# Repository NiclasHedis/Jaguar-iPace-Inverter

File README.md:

# Jaguar-iPace-Inverter
Design of Opensource Logic boards to run the Jaguar iPace Inverter and Motors.

PCB Designs in Kicad 9 format.

Front inverter used in the iPace is acuallly a Vitesco EPF2.8+ :
https://vitesco-technologies.com/en/Home/Solutions/Products/High-Voltage-Inverter-(EPF2-8-)-en

Reverse engineering thread on the openinverter forum :
https://openinverter.org/forum/viewtopic.php?f=23&t=1210

Videos :
https://youtu.be/Kg5qWuOF9P8

10/10/25 : Add prelim front drive unit V1 board design (work in progress).

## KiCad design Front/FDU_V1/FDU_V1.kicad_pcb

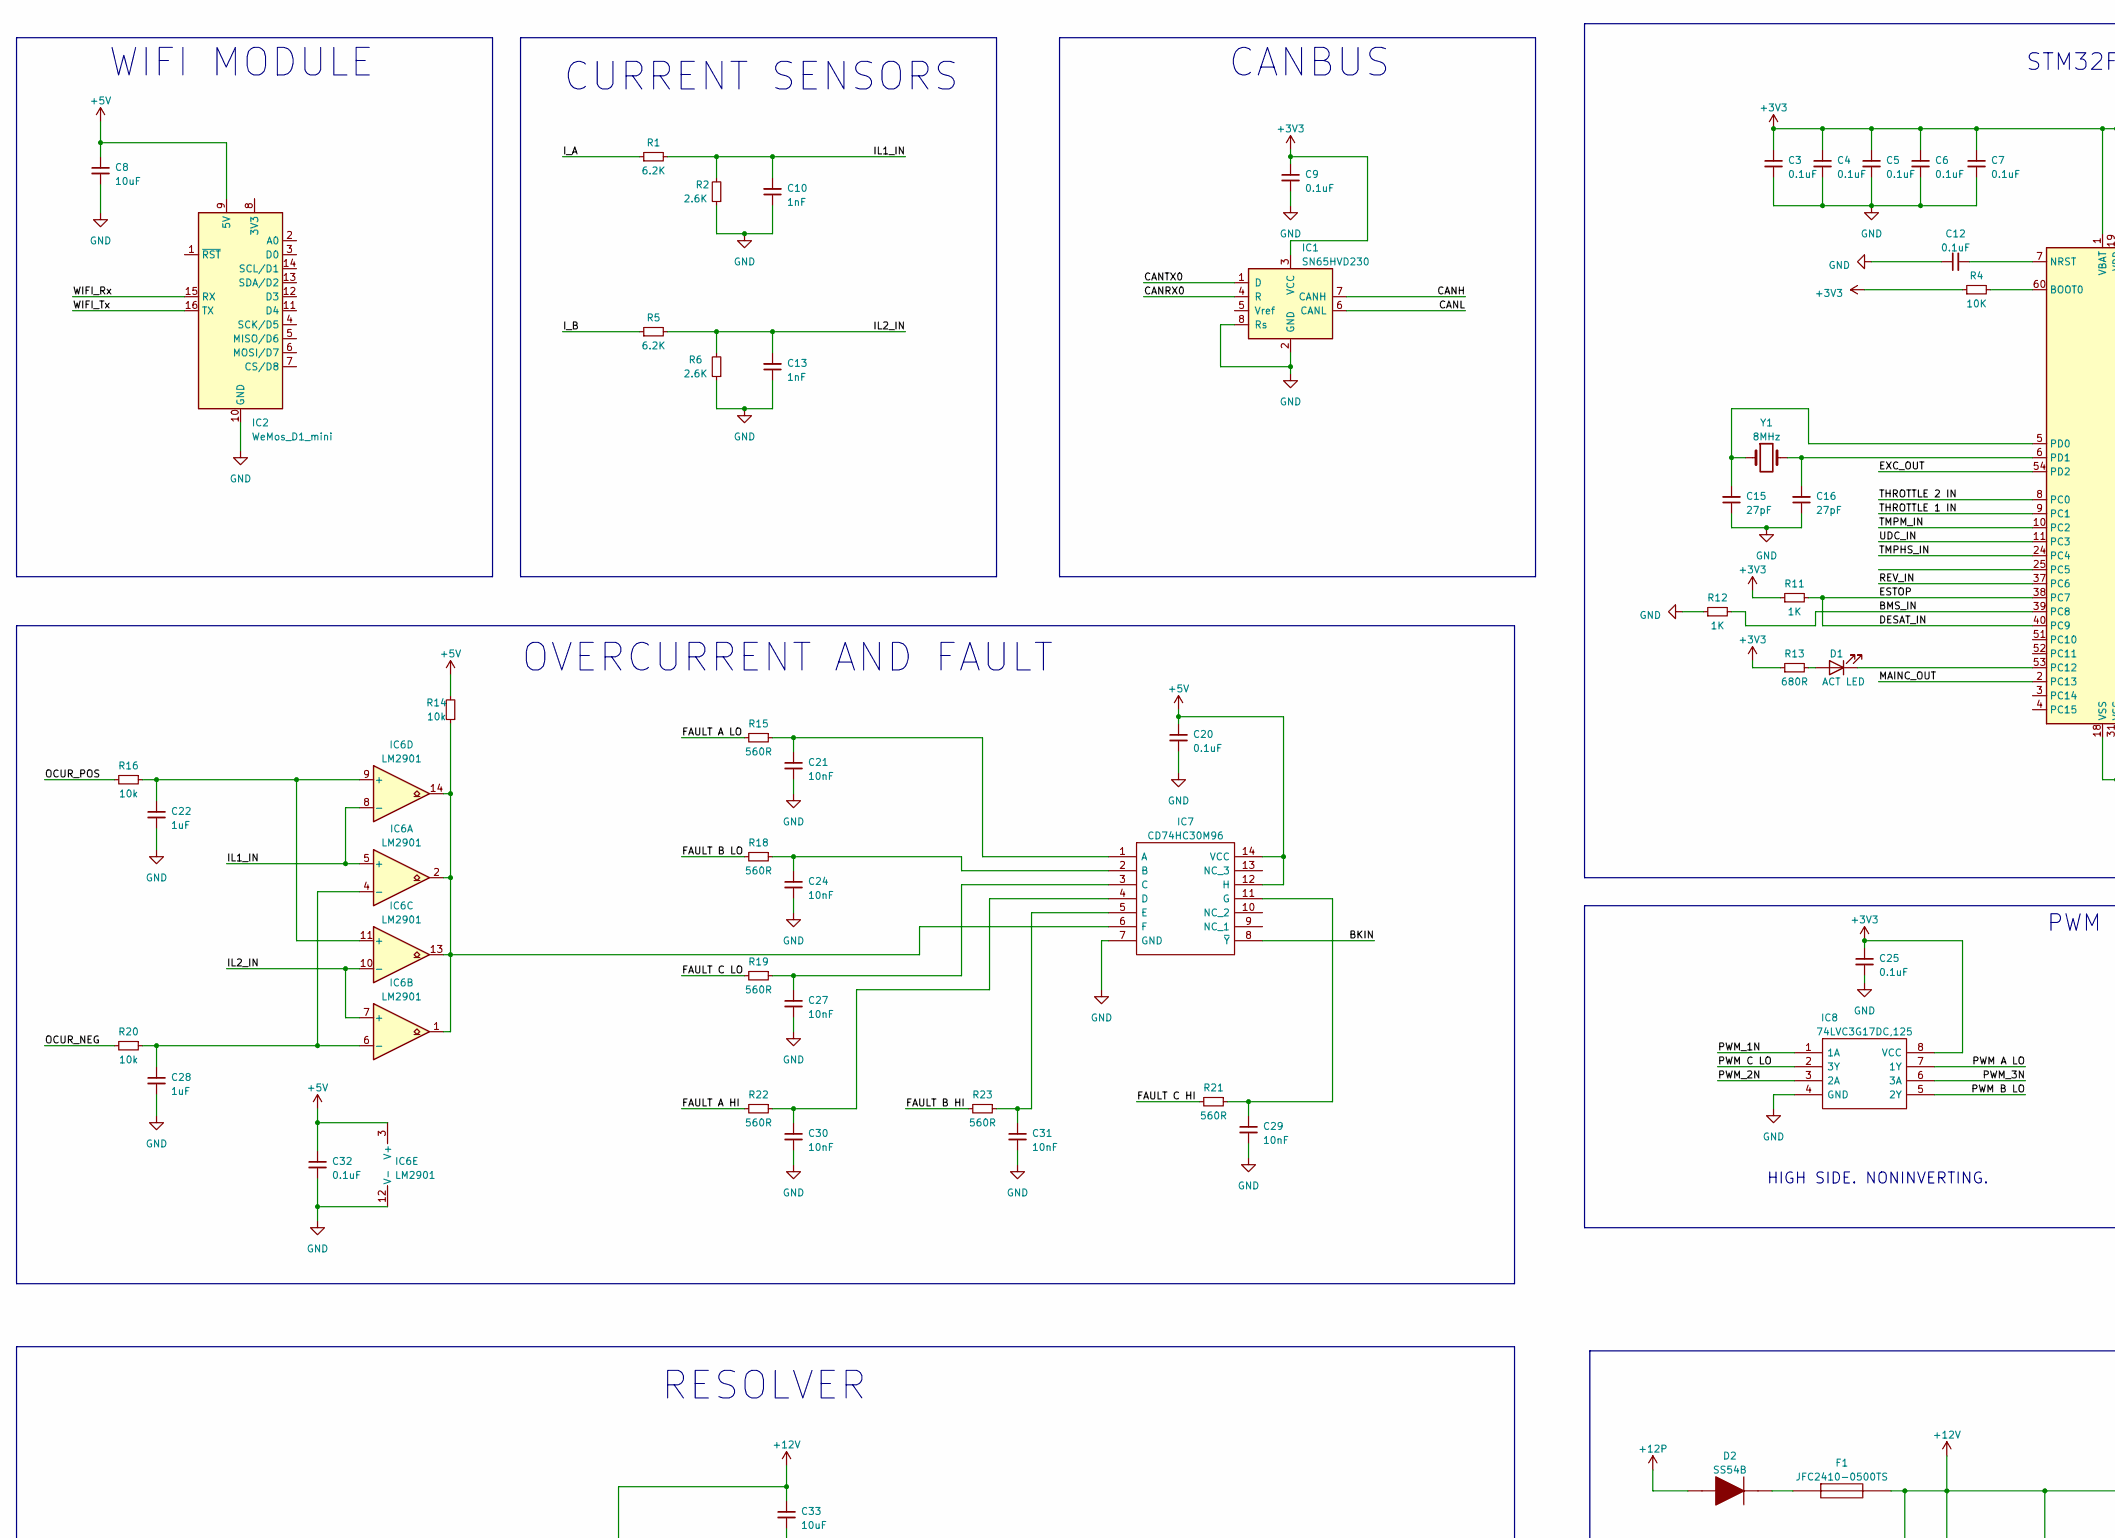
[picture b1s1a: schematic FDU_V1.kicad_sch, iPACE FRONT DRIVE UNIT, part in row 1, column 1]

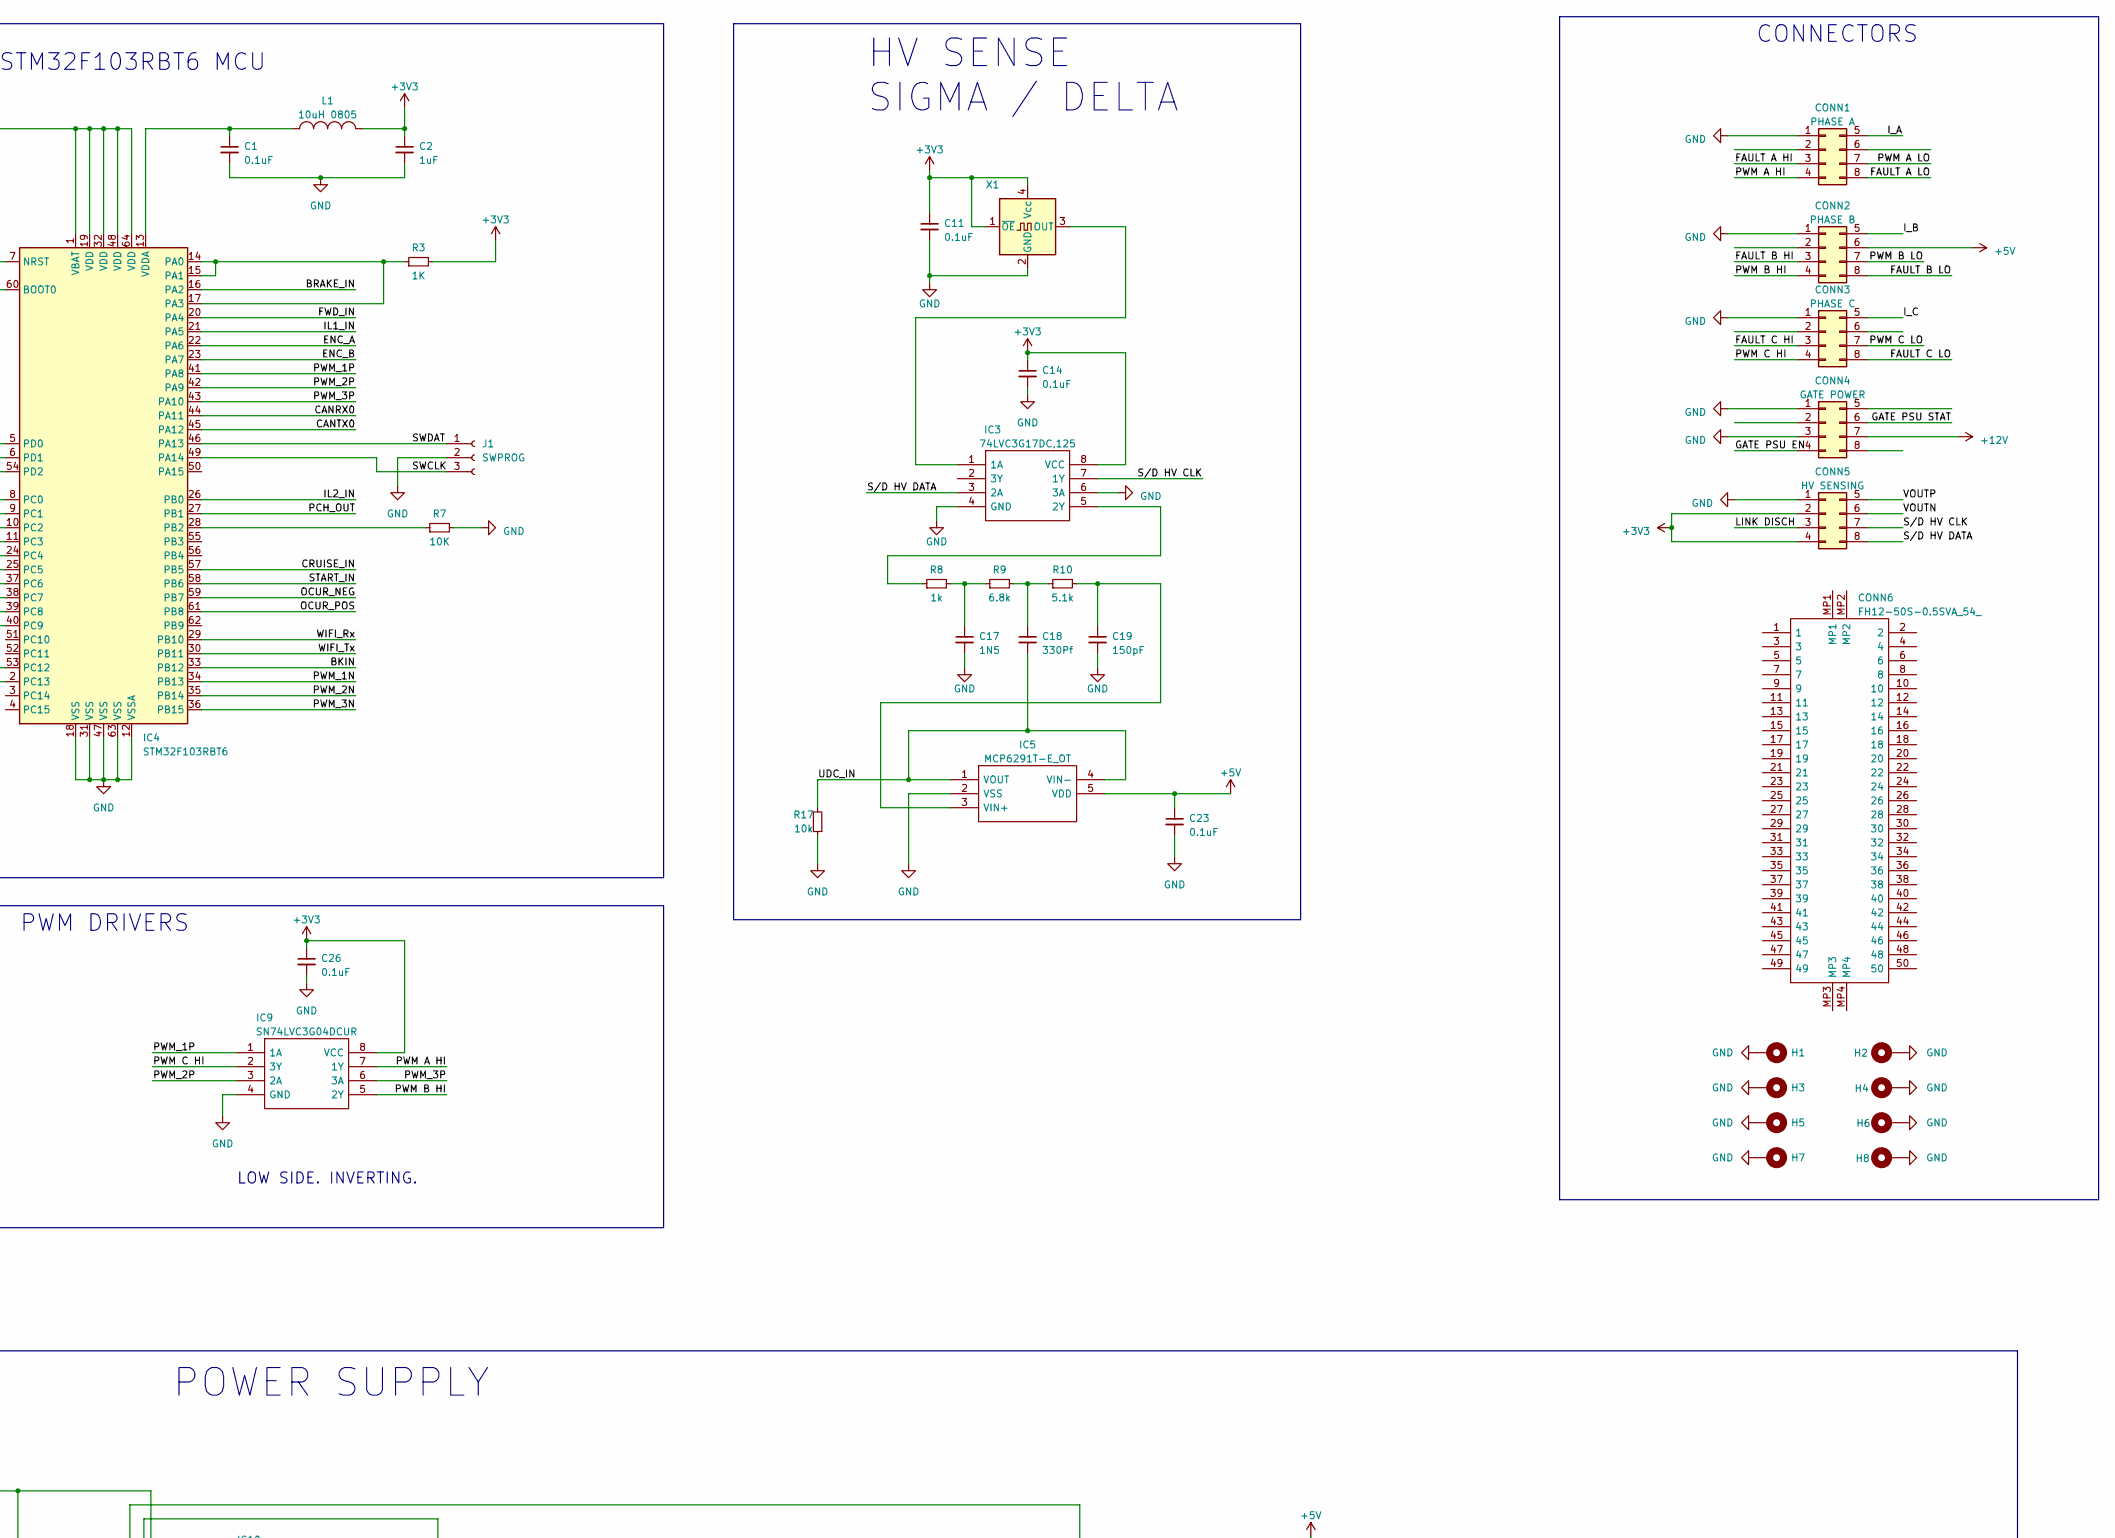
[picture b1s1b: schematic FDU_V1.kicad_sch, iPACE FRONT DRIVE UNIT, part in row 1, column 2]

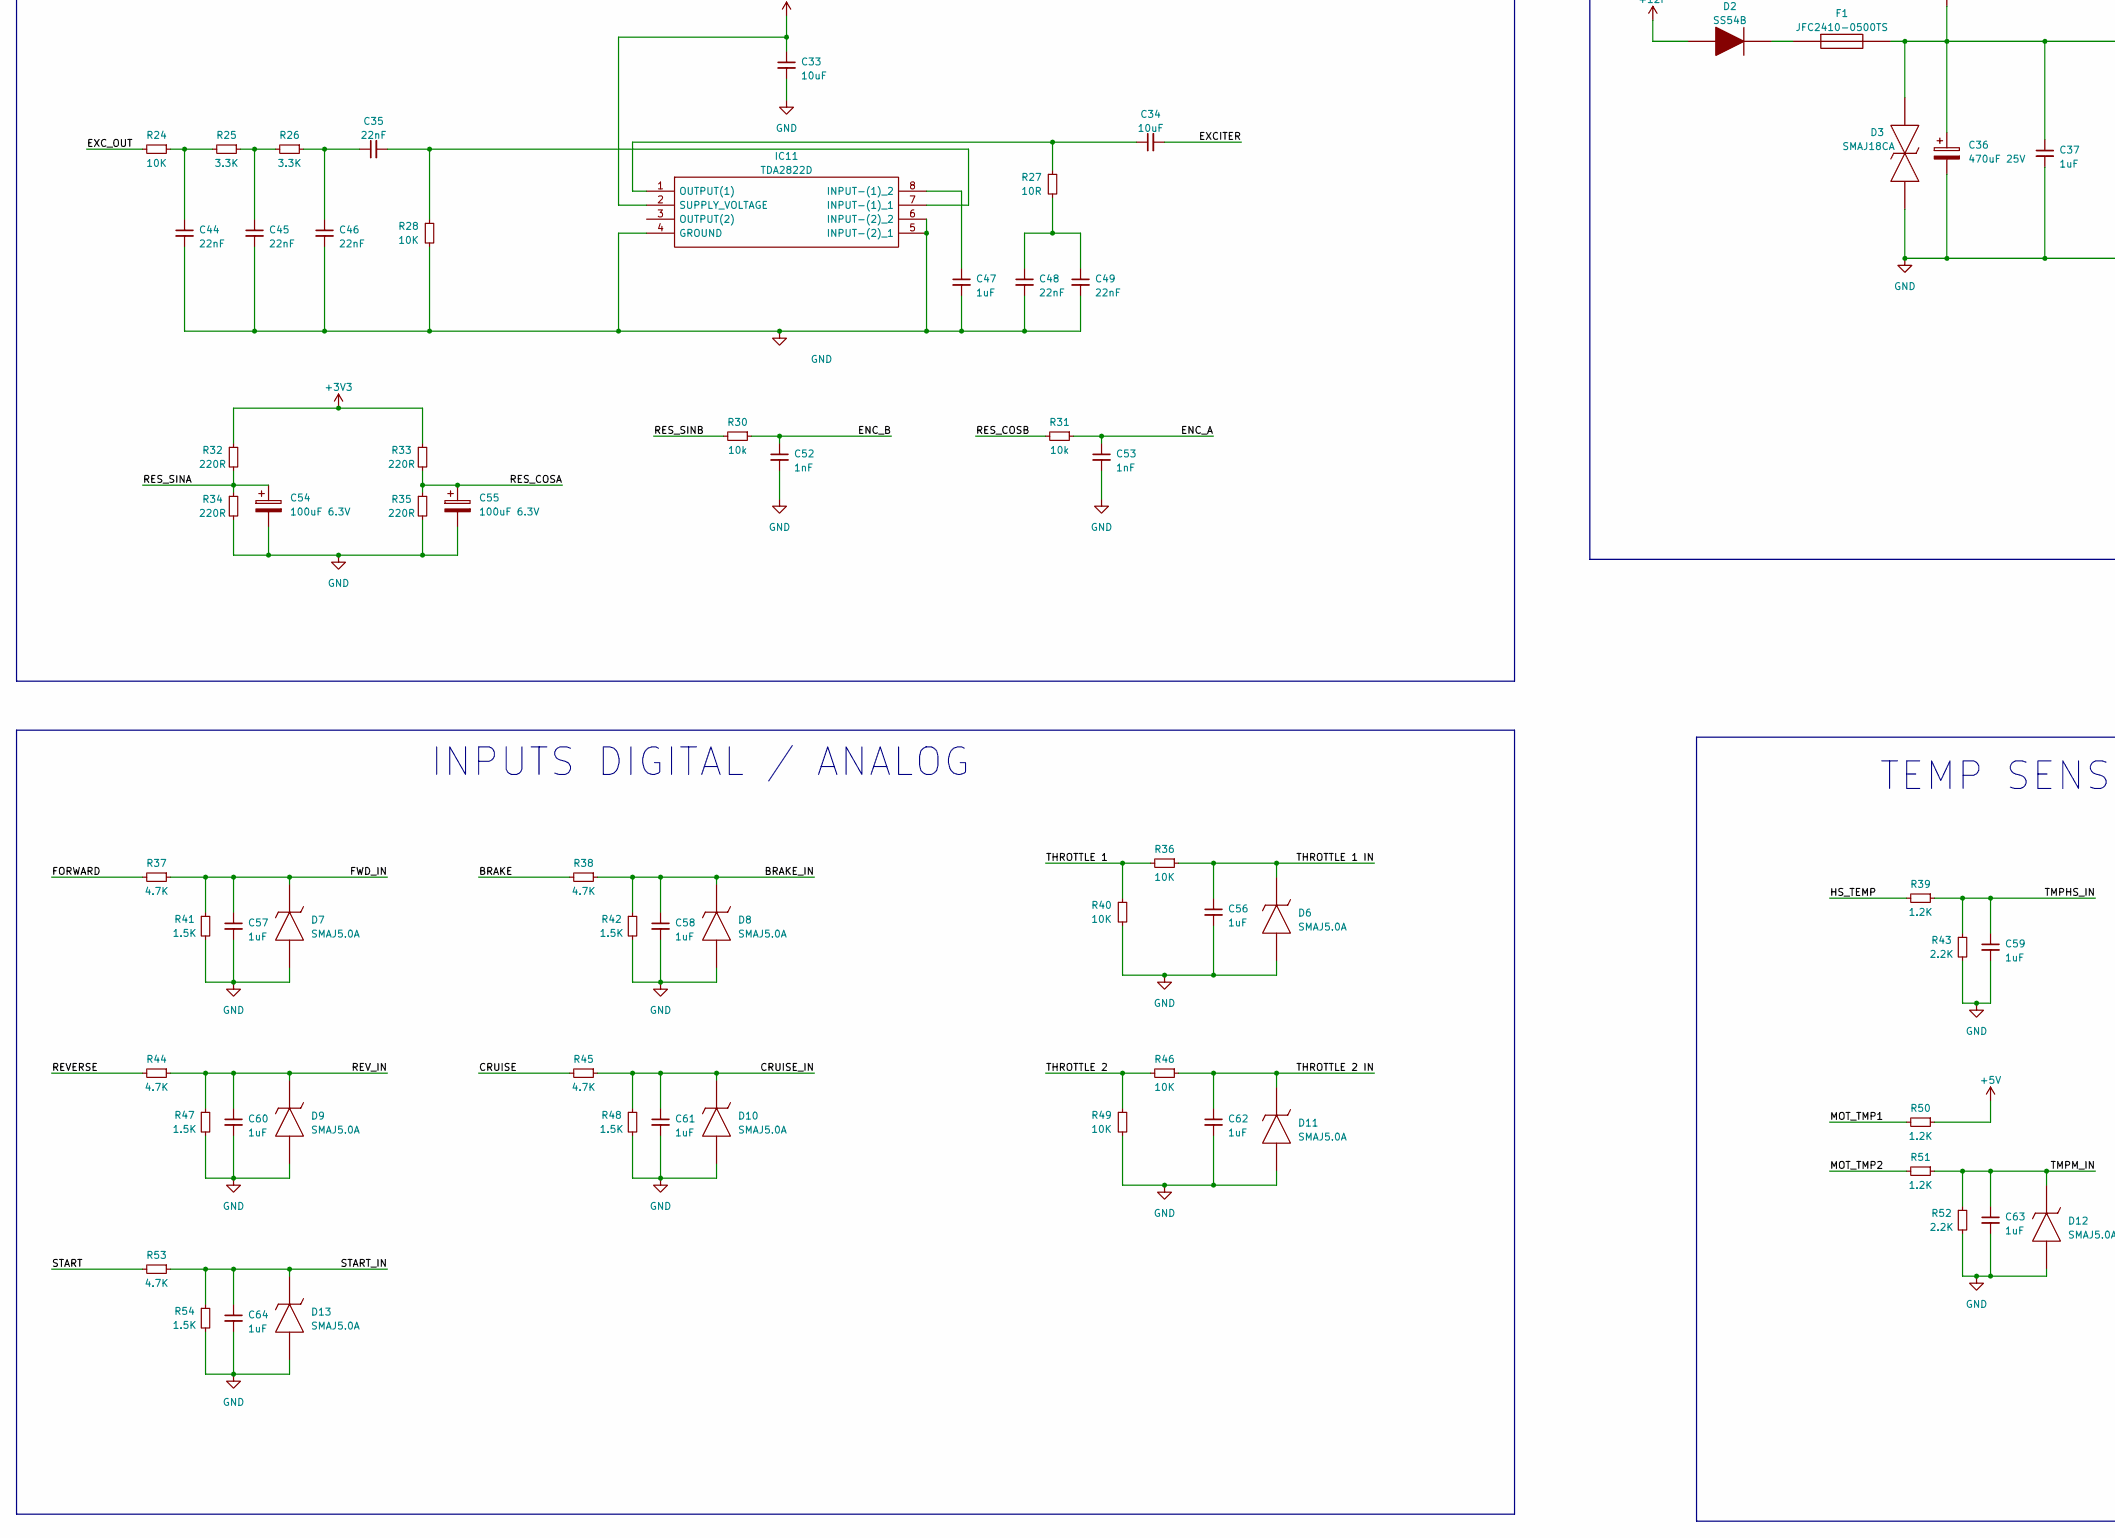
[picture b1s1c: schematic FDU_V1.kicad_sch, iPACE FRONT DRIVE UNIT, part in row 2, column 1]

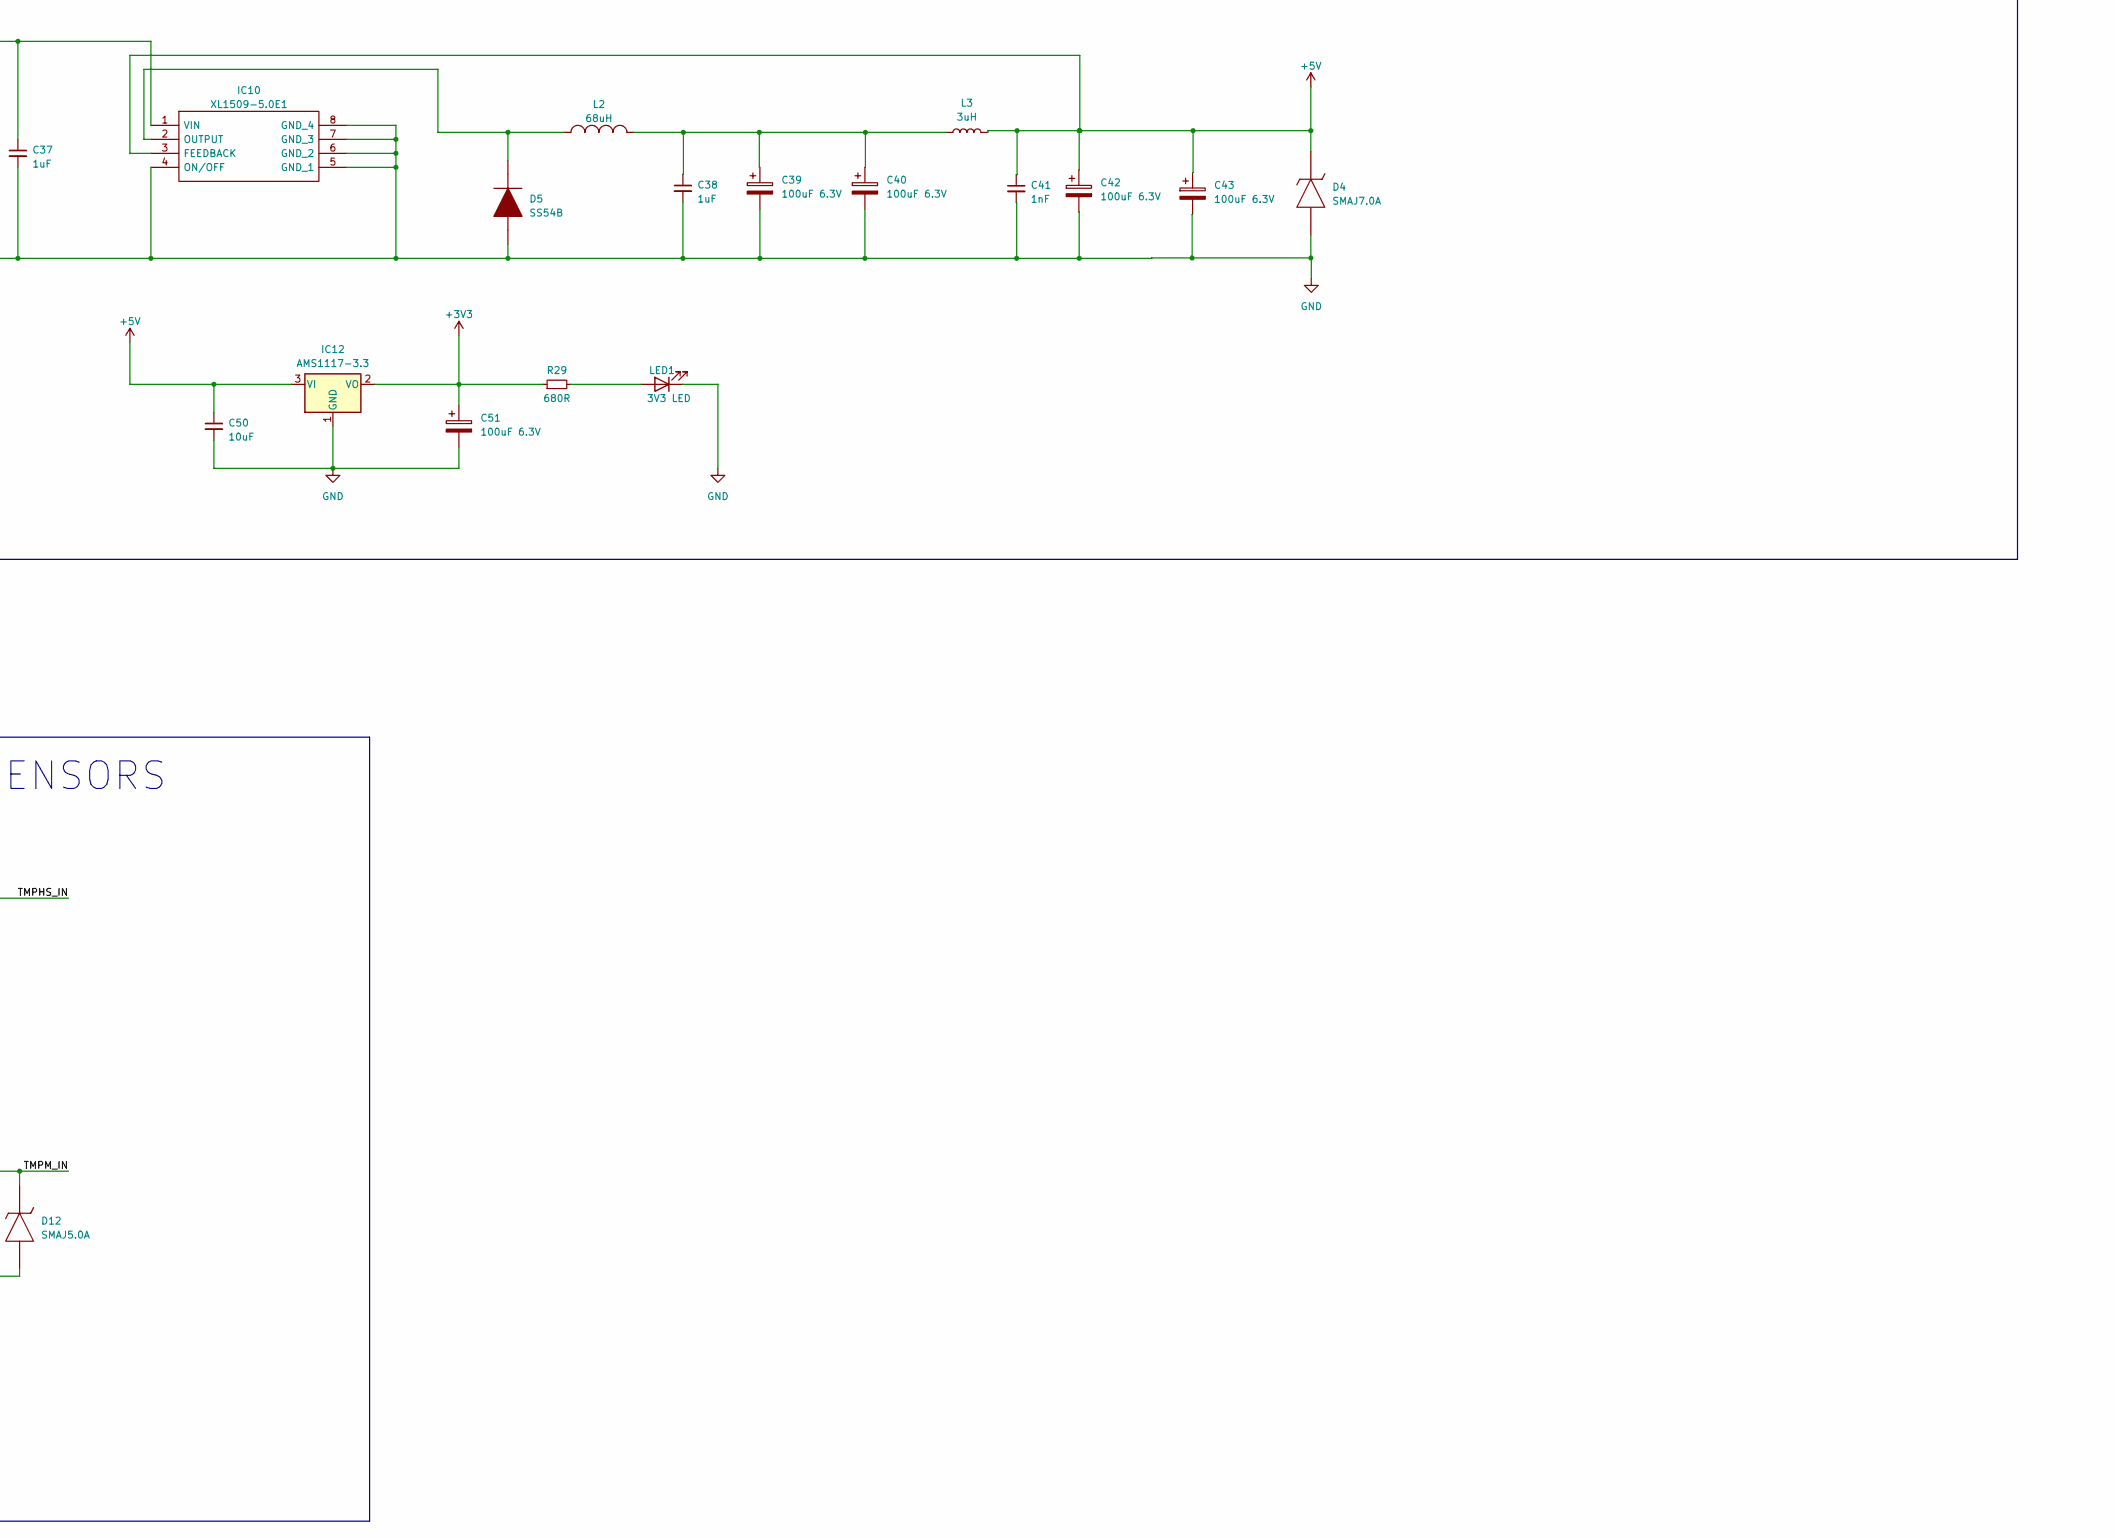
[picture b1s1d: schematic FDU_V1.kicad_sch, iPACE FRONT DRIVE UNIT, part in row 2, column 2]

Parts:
C1, C3, C4, C5, C6, C7, C9, C11, C12, C14, C20, C23, C25, C26, C32: 0.1uF; C_0805_2012Metric
C2, C22, C28, C37, C38, C47, C56, C57, C58, C59, C60, C61, C62, C63, C64: 1uF; C_0805_2012Metric
C8, C33, C34, C50: 10uF; C_0805_2012Metric
C10, C13, C41, C52, C53: 1nF; C_0805_2012Metric
C15, C16: 27pF; C_0805_2012Metric
C17: 1N5; C_0805_2012Metric
C18: 330Pf; C_0805_2012Metric
C19: 150pF; C_0805_2012Metric
C21, C24, C27, C29, C30, C31: 10nF; C_0805_2012Metric
C35, C44, C45, C46, C48, C49: 22nF; C_0805_2012Metric
C36: 470uF 25V; CP_Elec_10x10
C39, C40, C42, C43, C51, C54, C55: 100uF 6.3V; CP_EIA-3528-15_AVX-H
CONN1: PHASE A; PinHeader_2x04_P2.54mm_Vertical
CONN2: PHASE B; PinHeader_2x04_P2.54mm_Vertical
CONN3: PHASE C; PinHeader_2x04_P2.54mm_Vertical
CONN4: GATE POWER; PinHeader_2x04_P2.54mm_Vertical
CONN5: HV SENSING; PinHeader_2x04_P2.54mm_Vertical
CONN6: FH12-50S-0.5SVA_54_; FH1250S05SVA54; Manufacturer_Part_Number FH12-50S-0.5SVA(54); Mouser Part Number 798-FH1250S0.5SVA54
D1: ACT LED; LED_0805_2012Metric
D2, D5: SS54B; DIOM5336X244N; Manufacturer_Part_Number SS54B
D3: SMAJ18CA; DIONM5127X229N; Manufacturer_Part_Number SMAJ18CA; Mouser Part Number 652-SMAJ18CA
D4: SMAJ7.0A; DIOM5026X229N; Manufacturer_Part_Number SMAJ7.0A; Mouser Part Number 576-SMAJ7.0A
D6, D7, D8, D9, D10, D11, D12, D13: SMAJ5.0A; DIOM5127X229N; Manufacturer_Part_Number SMAJ5.0A; Mouser Part Number 78-SMAJ5.0A
F1: JFC2410-0500TS; FUSC6126X280N; Manufacturer_Part_Number JFC2410-0500TS
H1: MountingHole; MountingHole_8.4mm_M8_Pad_Via
H2, H3, H4, H5, H6, H7, H8: MountingHole; MountingHole_8mm_ipace
IC1: SN65HVD230; SOIC-8_3.9x4.9mm_P1.27mm
IC2: WeMos_D1_mini; WEMOS_D1_mini_light
IC3, IC8: 74LVC3G17DC,125; SOP50P310X100-8N; Manufacturer_Part_Number 74LVC3G17DC,125; Mouser Part Number 771-LVC3G17DC125
IC4: STM32F103RBT6; LQFP-64_10x10mm_P0.5mm
IC5: MCP6291T-E_OT; SOT95P280X145-5N; Manufacturer_Part_Number MCP6291T-E/OT; Mouser Part Number 579-MCP6291T-E/OT
IC6: LM2901; SOIC-14_3.9x8.7mm_P1.27mm
IC7: CD74HC30M96; SOIC127P600X175-14N; Manufacturer_Part_Number CD74HC30M96; Mouser Part Number 595-CD74HC30M96
IC9: SN74LVC3G04DCUR; SOP50P310X90-8N; Manufacturer_Part_Number SN74LVC3G04DCUR; Mouser Part Number 595-SN74LVC3G04DCUR
IC10: XL1509-5.0E1; SOIC127P600X175-8N; Manufacturer_Part_Number XL1509-5.0E1
IC11: TDA2822D; SOIC127P600X175-8N; Manufacturer_Part_Number TDA2822D; Mouser Part Number 511-TDA2822D
IC12: AMS1117-3.3; SOT-223-3_TabPin2
J1: SWPROG; PinHeader_1x03_P2.54mm_Vertical
L1: 10uH 0805; L_0805_2012Metric
L2: 68uH; L_12x12mm_H8mm
L3: 3uH; L_10.4x10.4_H4.8
LED1: 3V3 LED; LED_0805_2012Metric
R1, R5: 6.2K; R_0805_2012Metric
R2, R6: 2.6K; R_0805_2012Metric
R3, R11, R12: 1K; R_0805_2012Metric
R4, R7, R24, R28, R36, R40, R46, R49: 10K; R_0805_2012Metric
R8: 1k; R_0805_2012Metric
R9: 6.8k; R_0805_2012Metric
R10: 5.1k; R_0805_2012Metric
R13, R29: 680R; R_0805_2012Metric
R14, R16, R17, R20, R30, R31: 10k; R_0805_2012Metric
R15, R18, R19, R21, R22, R23: 560R; R_0805_2012Metric
R25, R26: 3.3K; R_0805_2012Metric
R27: 10R; R_0805_2012Metric
R32, R33, R34, R35: 220R; R_0805_2012Metric
R37, R38, R44, R45, R53: 4.7K; R_0805_2012Metric
R39, R50, R51: 1.2K; R_0805_2012Metric
R41, R42, R47, R48, R54: 1.5K; R_0805_2012Metric
R43, R52: 2.2K; R_0805_2012Metric
X1: S3D4.000000B20F30T; Oscillator_SMD_EuroQuartz_XO32-4Pin_3.2x2.5mm
Y1: 8MHz; Crystal_SMD_5032-2Pin_5.0x3.2mm

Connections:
+3V3: C2.1, C3.1, C4.1, C5.1, C6.1, C7.1, C9.1, C11.1, C14.1, C25.1, C26.1, C51.1, CONN5.2, CONN5.4, IC1.3 (VCC), IC3.8 (VCC), IC4.1 (VBAT), IC4.19 (VDD), IC4.32 (VDD), IC4.48 (VDD), IC4.64 (VDD), IC8.8 (VCC), IC9.8 (VCC), IC12.2 (VO), L1.2, R3.2, R4.1, R11.1, R13.1, R29.1, R32.1, R33.1, X1.1 (~OE), X1.4 (Vcc)
+5V: C8.1, C20.1, C23.1, C32.1, C41.1, C42.1, C43.1, C50.1, CONN2.6, D4.1, IC2.9 (5V), IC5.5 (VDD), IC6.3 (V+), IC7.12 (H), IC7.14 (VCC), IC10.3 (FEEDBACK), IC12.3 (VI), L3.2, R14.2, R50.1; also elsewhere on the board
+12P: CONN6.28, CONN6.29, CONN6.30, CONN6.31, CONN6.32, CONN6.33, CONN6.34, CONN6.35, CONN6.36, CONN6.37, CONN6.38, CONN6.39, CONN6.40, CONN6.41, CONN6.42, CONN6.43, CONN6.44, CONN6.45, CONN6.46, CONN6.47, CONN6.48, CONN6.49, CONN6.50, D2.2
+12V: C33.1, C36.1, C37.1, CONN4.7, D3.1, F1.2, IC10.1 (VIN), IC11.2 (SUPPLY_VOLTAGE)
/BKIN: IC4.33 (PB12), IC7.8 (~Y)
/BMS_IN: IC4.39 (PC8), R12.2
/BRAKE: CONN6.14, R38.2
/BRAKE_IN: C58.1, D8.1, IC4.16 (PA2), R38.1, R42.1
/CANH: CONN6.1, IC1.7 (CANH)
/CANL: CONN6.2, IC1.6 (CANL)
/CANRX0: IC1.4 (R), IC4.44 (PA11)
/CANTX0: IC1.1 (D), IC4.45 (PA12)
/CRUISE: CONN6.22, R45.2
/CRUISE_IN: C61.1, D10.1, IC4.57 (PB5), R45.1, R48.1
/DESAT_IN: IC4.38 (PC7), IC4.40 (PC9), R11.2
/ENC_A: C53.1, IC4.22 (PA6), R31.1
/ENC_B: C52.1, IC4.23 (PA7), R30.1
/EXCA: C34.2, CONN6.17
/EXCB: CONN6.18; also elsewhere on the board
/EXC_OUT: IC4.54 (PD2), R24.2
/FAULT A HI: CONN1.3, R22.2
/FAULT A LO: CONN1.8, R15.2
/FAULT B HI: CONN2.3, R23.2
/FAULT B LO: CONN2.8, R18.2
/FAULT C HI: CONN3.3, R21.2
/FAULT C LO: CONN3.8, R19.2
/FORWARD: CONN6.7, R37.2
/FWD_IN: C57.1, D7.1, IC4.20 (PA4), R37.1, R41.1
/GATE PSU EN: CONN4.4
/GATE PSU STAT: CONN4.6
/HS_TEMP: R39.2
/IL1_IN: C10.2, IC4.21 (PA5), IC6.5 (+), IC6.8 (-), R1.2, R2.2
/IL2_IN: C13.2, IC4.26 (PB0), IC6.7 (+), IC6.10 (-), R5.2, R6.2
/I_A: CONN1.5, R1.1
/I_B: CONN2.5, R5.1
/I_C: CONN3.5
/LINK DISCH: CONN5.3
/MAINC_OUT: IC4.2 (PC13)
/MOT_TMP1_1: CONN6.9, R50.2
/MOT_TMP1_2: CONN6.10, R51.2
/MOT_TMP2_1: CONN6.11; also elsewhere on the board
/MOT_TMP2_2: CONN6.12; also elsewhere on the board
/OCUR_NEG: IC4.59 (PB7), R20.2
/OCUR_POS: IC4.61 (PB8), R16.2
/PCH_OUT: IC4.27 (PB1)
/PWM A HI: CONN1.4, IC9.7 (1Y)
/PWM A LO: CONN1.7, IC8.7 (1Y)
/PWM B HI: CONN2.4, IC9.5 (2Y)
/PWM B LO: CONN2.7, IC8.5 (2Y)
/PWM C HI: CONN3.4, IC9.2 (3Y)
/PWM C LO: CONN3.7, IC8.2 (3Y)
/PWM_1N: IC4.34 (PB13), IC8.1 (1A)
/PWM_1P: IC4.41 (PA8), IC9.1 (1A)
/PWM_2N: IC4.35 (PB14), IC8.3 (2A)
/PWM_2P: IC4.42 (PA9), IC9.3 (2A)
/PWM_3N: IC4.36 (PB15), IC8.6 (3A)
/PWM_3P: IC4.43 (PA10), IC9.6 (3A)
/RES_COSA: C55.1, CONN6.21, R33.2, R35.1
/RES_COSB: CONN6.20, R31.2
/RES_SINA: C54.1, CONN6.23, R32.2, R34.1
/RES_SINB: CONN6.24, R30.2
/REVERSE: CONN6.8, R44.2
/REV_IN: C60.1, D9.1, IC4.37 (PC6), R44.1, R47.1
/START: CONN6.3, R53.2
/START_IN: C64.1, D13.1, IC4.58 (PB6), R53.1, R54.1
/SWCLK: IC4.49 (PA14), J1.3
/SWDAT: IC4.46 (PA13), J1.1
/S/D HV CLK: CONN5.7, IC3.7 (1Y)
/S/D HV DATA: CONN5.8, IC3.3 (2A)
/THROTTLE 1: CONN6.15, R36.2, R40.1
/THROTTLE 1 IN: C56.1, D6.1, IC4.9 (PC1), R36.1
/THROTTLE 2: CONN6.16, R46.2, R49.1
/THROTTLE 2 IN: C62.1, D11.1, IC4.8 (PC0), R46.1
/TMPHS_IN: C59.1, IC4.24 (PC4), R39.1, R43.1
/UDC_IN: C18.2, IC4.11 (PC3), IC5.1 (VOUT), IC5.4 (VIN-), R17.2
/VOUTN: CONN5.6
/VOUTP: CONN5.5
/WIFI_Rx: IC2.15 (RX), IC4.29 (PB10)
/WIFI_Tx: IC2.16 (TX), IC4.30 (PB11)
/WTR_TMP1: CONN6.5; also elsewhere on the board
/WTR_TMP2: CONN6.6; also elsewhere on the board
GND: C1.2, C2.2, C3.2, C4.2, C5.2, C6.2, C7.2, C8.2, C9.2, C10.1, C11.2, C12.1, C13.1, C14.2, C15.1, C16.1, C17.2, C19.2, C20.2, C21.2, C22.2, C23.2, C24.2, C25.2, C26.2, C27.2, C28.2, C29.2, C30.2, C31.2, C32.2, C33.2, C36.2, C37.2, C38.2, C39.2, C40.2, C41.2, C42.2, C43.2, C44.2, C45.2, C46.2, C47.2, C48.2, C49.2, C50.2, C51.2, C52.2, C53.2, C54.2, C55.2, C56.2, C57.2, C58.2, C59.2, C60.2, C61.2, C62.2, C63.2, C64.2, CONN1.1, CONN2.1, CONN3.1, CONN4.1, CONN4.3, CONN5.1, D3.2, D4.2, D5.2, D6.2, D7.2, D8.2, D9.2, D10.2, D11.2, D12.2, D13.2, H1.1, H2.1, H3.1, H4.1, H5.1, H6.1, H7.1, H8.1, IC1.2 (GND), IC1.8 (Rs), IC2.10 (GND), IC3.4 (GND), IC3.6 (3A), IC4.12 (VSSA), IC4.18 (VSS), IC4.31 (VSS), IC4.47 (VSS), IC4.63 (VSS), IC5.2 (VSS), IC6.12 (V-), IC7.7 (GND), IC8.4 (GND), IC9.4 (GND), IC10.4 (ON/OFF), IC10.5 (GND_1), IC10.6 (GND_2), IC10.7 (GND_3), IC10.8 (GND_4), IC11.4 (GROUND), IC11.5 (INPUT-(2)_1), IC11.6 (INPUT-(2)_2), IC12.1 (GND), J1.2, LED1.1 (K), R2.1, R6.1, R7.2, R12.1, R17.1, R28.2, R34.2, R35.2, R40.2, R41.2, R42.2, R43.2, R47.2, R48.2, R49.2, R52.2, R54.2, X1.2 (GND); also elsewhere on the board
unnamed: C17.1, R8.2, R9.1
unnamed: C18.1, R9.2, R10.1
unnamed: C35.1, C46.1, R26.1
unnamed: C38.1, C39.1, C40.1, L2.2, L3.1
unnamed: C44.1, R24.1, R25.2
unnamed: C45.1, R25.1, R26.2
unnamed: C48.1, C49.1, R27.2
unnamed: D1.2 (A), R13.2
unnamed: D1.1 (K), IC4.53 (PC12)
unnamed: D2.1, F1.1
unnamed: IC3.1 (1A), X1.3 (OUT)
unnamed: IC3.5 (2Y), R8.1
unnamed: IC4.60 (BOOT0), R4.2
unnamed: C12.2, IC4.7 (NRST)
unnamed: IC4.14 (PA0), IC4.15 (PA1), IC4.17 (PA3), R3.1
unnamed: IC4.28 (PB2), R7.1
unnamed: C15.2, IC4.5 (PD0), Y1.1
unnamed: C16.2, IC4.6 (PD1), Y1.2
unnamed: C1.1, IC4.13 (VDDA), L1.1
unnamed: C19.1, IC5.3 (VIN+), R10.2
unnamed: C28.1, IC6.4 (-), IC6.6 (-), R20.1
unnamed: C22.1, IC6.9 (+), IC6.11 (+), R16.1
unnamed: C21.1, IC7.1 (A), R15.1
unnamed: C24.1, IC7.2 (B), R18.1
unnamed: C27.1, IC7.3 (C), R19.1
unnamed: C30.1, IC7.4 (D), R22.1
unnamed: C31.1, IC7.5 (E), R23.1
unnamed: IC6.1, IC6.2, IC6.13, IC6.14, IC7.6 (F), R14.1
unnamed: C29.1, IC7.11 (G), R21.1
unnamed: D5.1, IC10.2 (OUTPUT), L2.1
unnamed: C35.2, IC11.7 (INPUT-(1)_1), R28.1
unnamed: C47.1, IC11.8 (INPUT-(1)_2)
unnamed: C34.1, IC11.1 (OUTPUT(1)), R27.1
unnamed: LED1.2 (A), R29.2

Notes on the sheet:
WIFI MODULE
PWM DRIVERS
POWER SUPPLY
CONNECTORS
CURRENT SENSORS
RESOLVER
OVERCURRENT AND FAULT
STM32F103RBT6 MCU
HIGH SIDE. NONINVERTING.
LOW SIDE. INVERTING.
HV SENSE SIGMA / DELTA
INPUTS DIGITAL / ANALOG
CANBUS
TEMP SENSORS

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
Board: 4 copper layers, 174 parts (0 on the bottom side), 108 nets, no tracks yet.

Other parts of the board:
C65, C66: 1uF; C_0805_2012Metric
R55, R56, R58, R60: 1.2K; R_0805_2012Metric
R57, R61: 2.2K; R_0805_2012Metric
R59: 0K; R_0805_2012Metric

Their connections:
+5V: R55.1, R58.1; also elsewhere on the board
/EXCB: R59.1; also elsewhere on the board
/MOT_TMP2_1: R58.2; also elsewhere on the board
/MOT_TMP2_2: R60.2; also elsewhere on the board
/TMPM2_IN: C66.1, R60.1, R61.1
/TMPWTR_IN: C65.1, R56.1, R57.1
/WTR_TMP1: R55.2; also elsewhere on the board
/WTR_TMP2: R56.2; also elsewhere on the board
GND: C65.2, C66.2, R57.2, R59.2, R61.2; also elsewhere on the board

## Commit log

2025-10-10 Add FDU V1 wip
2025-11-07 Continued work on both schematic and board placement.
    Schematic: Pinout added for external 28pin connector.
    PCB: Corrected board outline dimensions and all external dependencies. (holes, pin headers, ZIP connector)
2026-03-10 Changed microcontroller to 100pin

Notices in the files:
Front/FDU_V1/FDU_V1.kicad_pcb:
©2025 D.MAGUIRE,J.HÜBNER,N.HEDLUND
